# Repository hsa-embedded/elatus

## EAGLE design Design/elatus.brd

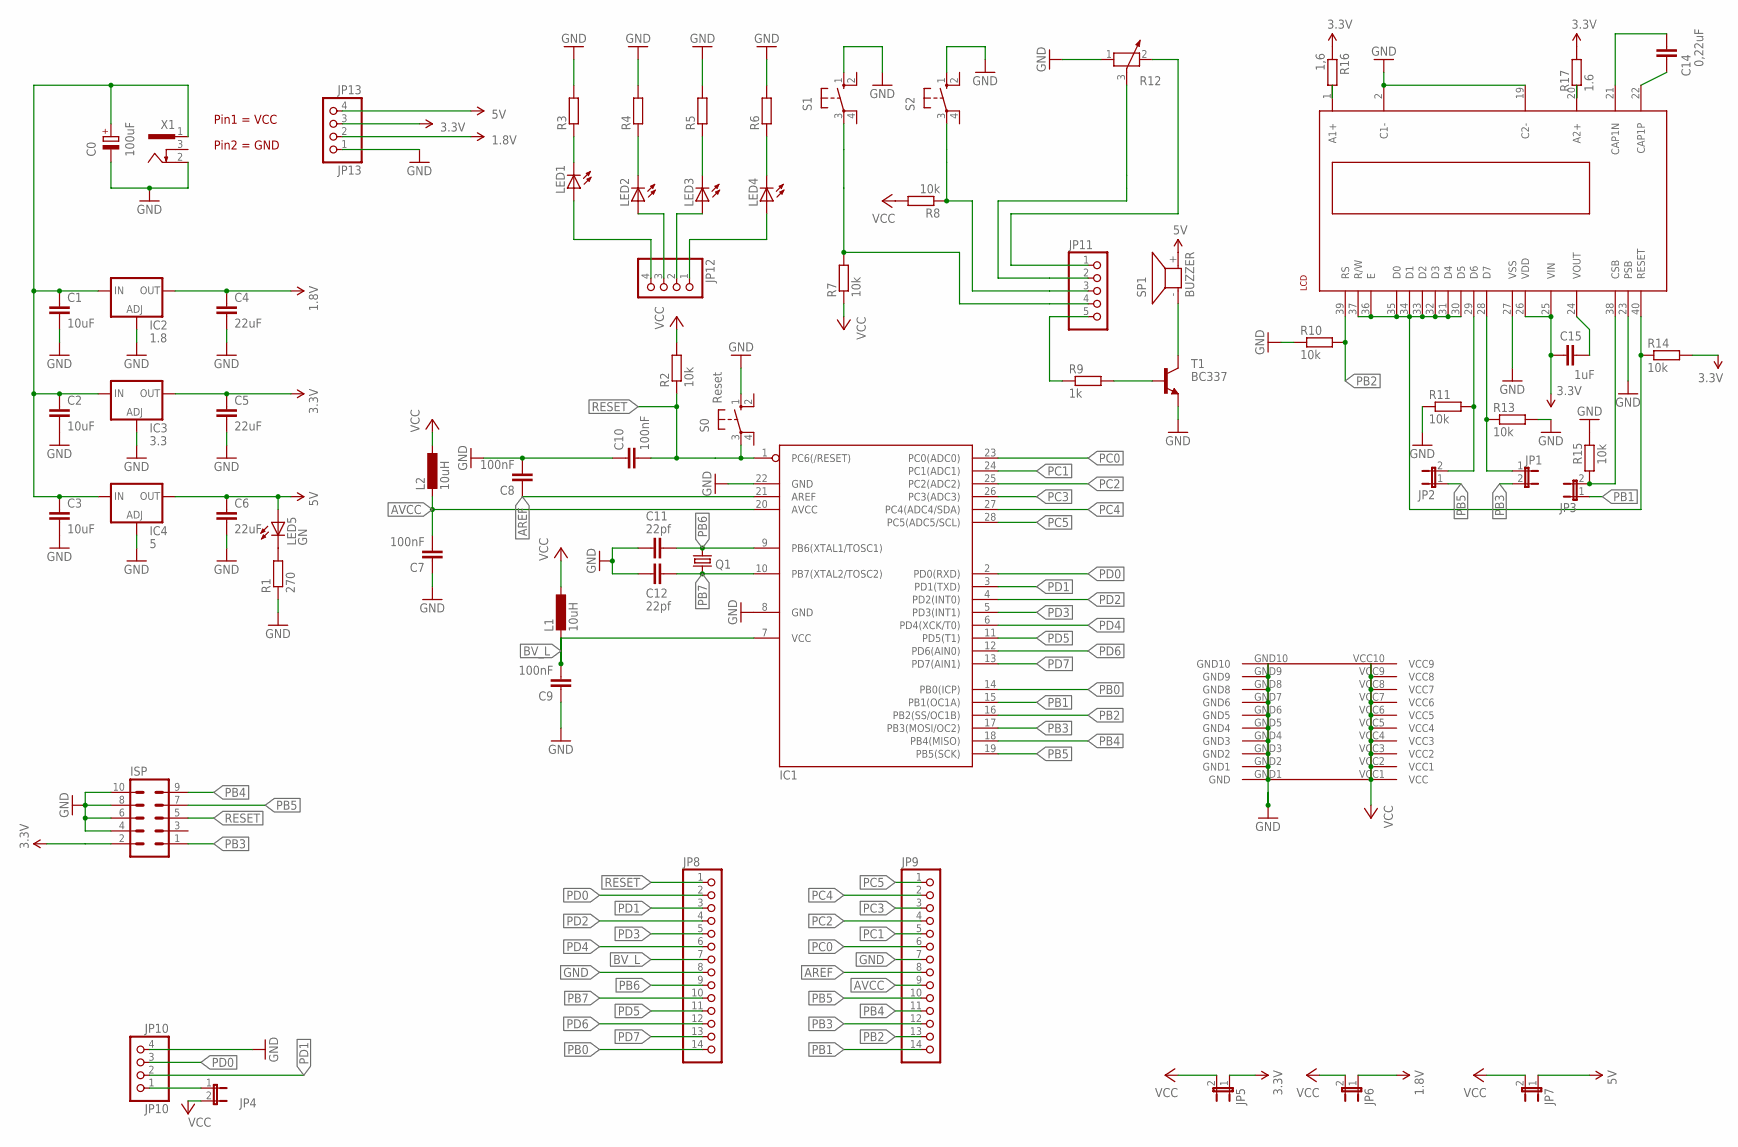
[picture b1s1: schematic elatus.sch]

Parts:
C0: 100uF; RCL_E2,5-7
C1, C2, C3: 10uF; RCL_C025-040X050
C4, C5, C6: 22uF; RCL_C025-040X050
C7, C8, C9, C10: 100nF; RCL_C025-040X050
C11, C12: 22pf; RESISTOR_C050-024X044
C14: 0,22uF; RCL_C025-040X050
C15: 1uF; RCL_C025-040X050
IC1: MEGA8-P; DIL28-3
IC2: 1.8; TO220V
IC3: 3.3; TO220V
IC4: 5; TO220V
ISP: CON-HARTING-ML_ML10
JP1, JP2, JP3, JP4, JP5, JP6, JP7: JP1E; JP1
JP8, JP9: PINHD-1X14; 1X14
JP10: JP10; 1X04
JP11: PINHD-1X5; 1X05
JP12: PINHD-1X4; 1X04
JP13: JP13; 1X04
L1, L2: 10uH; RCL_2200-12.7
LCD: -OPTO_DOGM
LED1, LED2, LED3, LED4: LED_LED3MM
LED5: GN; LED_LED3MM
Q1: CRYSTAL_CRYSTALHC49U70; CRYSTAL_HC49U70
R1: 270; 0207/10
R2, R7, R8, R10, R11, R13, R14, R15: 10k; 0207/10
R3, R4, R5, R6: R-EU_0207/10; 0207/10
R9: 1k; 0207/10
R12: POTENTIOMETER_PT-10; PT-10
R16: 1,6; 0207/10
R17: 1.6; 0207/10
S0: Reset; SWITCH-OMRON_B3F-10XX
S1, S2: SWITCH-OMRON_10-XX; SWITCH-OMRON_B3F-10XX
SP1: BUZZER; BUZZER_F/PMX04A
T1: BC337; TO92
U$3: JP5; RASTER_2_54
X1: CON-CONRAD_733980-62

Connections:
1.8V: C4.1, IC2.2 (OUT), JP6.1, JP13.2
3.3V: C5.1, C15.2, IC3.2 (OUT), ISP.2, JP5.1, JP13.3, LCD.25 (VIN), LCD.26 (VDD), R14.2, R16.1, R17.2
5V: C6.1, IC4.2 (OUT), JP7.1, JP13.4, LED5.A, SP1.+ (2)
AREF: C8.1, IC1.21 (AREF), JP9.8
AVCC: C7.2, IC1.20 (AVCC), JP9.9, L2.2
BV_L: C9.2, IC1.7 (VCC), JP8.7, L1.2
GND: C0.-, C1.2, C2.2, C3.2, C4.2, C5.2, C6.2, C7.1, C8.2, C9.1, C10.1, C11.1, C12.1, IC1.8 (GND), IC1.22 (GND), IC2.1 (ADJ), IC3.1 (ADJ), IC4.1 (ADJ), ISP.4, ISP.6, ISP.8, ISP.10, JP8.8, JP9.7, JP10.4, JP13.1, LCD.2 (C1-), LCD.19 (C2-), LCD.23 (PSB), LCD.27 (VSS), R1.1, R3.2, R4.2, R5.2, R6.2, R10.1, R11.1, R12.1, R13.2, R15.2, S0.1 (S), S1.1 (S), S2.1 (S), T1.1 (E), U$3.GND1 (GND), U$3.GND2 (GND1), U$3.GND3 (GND2), U$3.GND4 (GND3), U$3.GND5 (GND4), U$3.GND6 (GND5), U$3.GND7 (GND6), U$3.GND8, U$3.GND9, U$3.GND10, X1.2
unnamed: LED1.K (C), R3.1
unnamed: LED2.K (C), R4.1
unnamed: JP11.2, R12.3
unnamed: LED3.K (C), R5.1
unnamed: JP11.4, R7.2, S1.3
unnamed: JP12.4, LED1.A
unnamed: JP11.3, R8.1, S2.3
unnamed: LED4.K (C), R6.1
unnamed: JP11.1, R12.2
unnamed: JP12.3, LED2.A
unnamed: JP2.2, LCD.29 (D6), R11.2
unnamed: JP1.1, LCD.28 (D7), R13.1
unnamed: LED5.K (C), R1.2
unnamed: JP4.1, JP10.1
unnamed: JP12.2, LED3.A
unnamed: JP11.5, R9.1
unnamed: JP12.1, LED4.A
unnamed: SP1.- (1), T1.3 (C)
unnamed: LCD.20 (A2+), R17.1
unnamed: C14.2, LCD.21 (CAP1N)
unnamed: C14.1, LCD.22 (CAP1P)
unnamed: C0.+, C1.1, C2.1, C3.1, IC2.3 (IN), IC3.3 (IN), IC4.3 (IN), X1.1
unnamed: LCD.1 (A1+), R16.2
unnamed: LCD.30 (D5), LCD.31 (D4), LCD.32 (D3), LCD.33 (D2), LCD.34 (D1), LCD.35 (D0), LCD.36 (E), LCD.37 (R/W), LCD.40 (RESET), R14.1
unnamed: R9.2, T1.2 (B)
unnamed: C15.1, LCD.24 (VOUT)
unnamed: JP3.2, LCD.38 (CSB), R15.1
PB0: IC1.14 (PB0(ICP)), JP8.14
PB1: IC1.15 (PB1(OC1A)), JP3.1, JP9.14
PB2: IC1.16 (PB2(SS/OC1B)), JP9.13, LCD.39 (RS), R10.2
PB3: IC1.17 (PB3(MOSI/OC2)), ISP.1, JP1.2, JP9.12
PB4: IC1.18 (PB4(MISO)), ISP.9, JP9.11
PB5: IC1.19 (PB5(SCK)), ISP.7, JP2.1, JP9.10
PB6: C11.2, IC1.9 (PB6(XTAL1/TOSC1)), JP8.9, Q1.2
PB7: C12.2, IC1.10 (PB7(XTAL2/TOSC2)), JP8.10, Q1.1
PC0: IC1.23 (PC0(ADC0)), JP9.6
PC1: IC1.24 (PC1(ADC1)), JP9.5
PC2: IC1.25 (PC2(ADC2)), JP9.4
PC3: IC1.26 (PC3(ADC3)), JP9.3
PC4: IC1.27 (PC4(ADC4/SDA)), JP9.2
PC5: IC1.28 (PC5(ADC5/SCL)), JP9.1
PD0: IC1.2 (PD0(RXD)), JP8.2, JP10.3
PD1: IC1.3 (PD1(TXD)), JP8.3, JP10.2
PD2: IC1.4 (PD2(INT0)), JP8.4
PD3: IC1.5 (PD3(INT1)), JP8.5
PD4: IC1.6 (PD4(XCK/T0)), JP8.6
PD5: IC1.11 (PD5(T1)), JP8.11
PD6: IC1.12 (PD6(AIN0)), JP8.12
PD7: IC1.13 (PD7(AIN1)), JP8.13
RESET: C10.2, IC1.1 (PC6(/RESET)), ISP.5, JP8.1, R2.1, S0.3
VCC: JP4.2, JP5.2, JP6.2, JP7.2, L1.1, L2.1, R2.2, R7.1, R8.2, U$3.VCC1 (VCC), U$3.VCC2 (VCC1), U$3.VCC3 (VCC2), U$3.VCC4 (VCC3), U$3.VCC5 (VCC4), U$3.VCC6 (VCC5), U$3.VCC7 (VCC6), U$3.VCC8 (VCC7), U$3.VCC9 (VCC8), U$3.VCC10 (VCC9)

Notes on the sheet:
Pin1 = VCC
Pin2 = GND

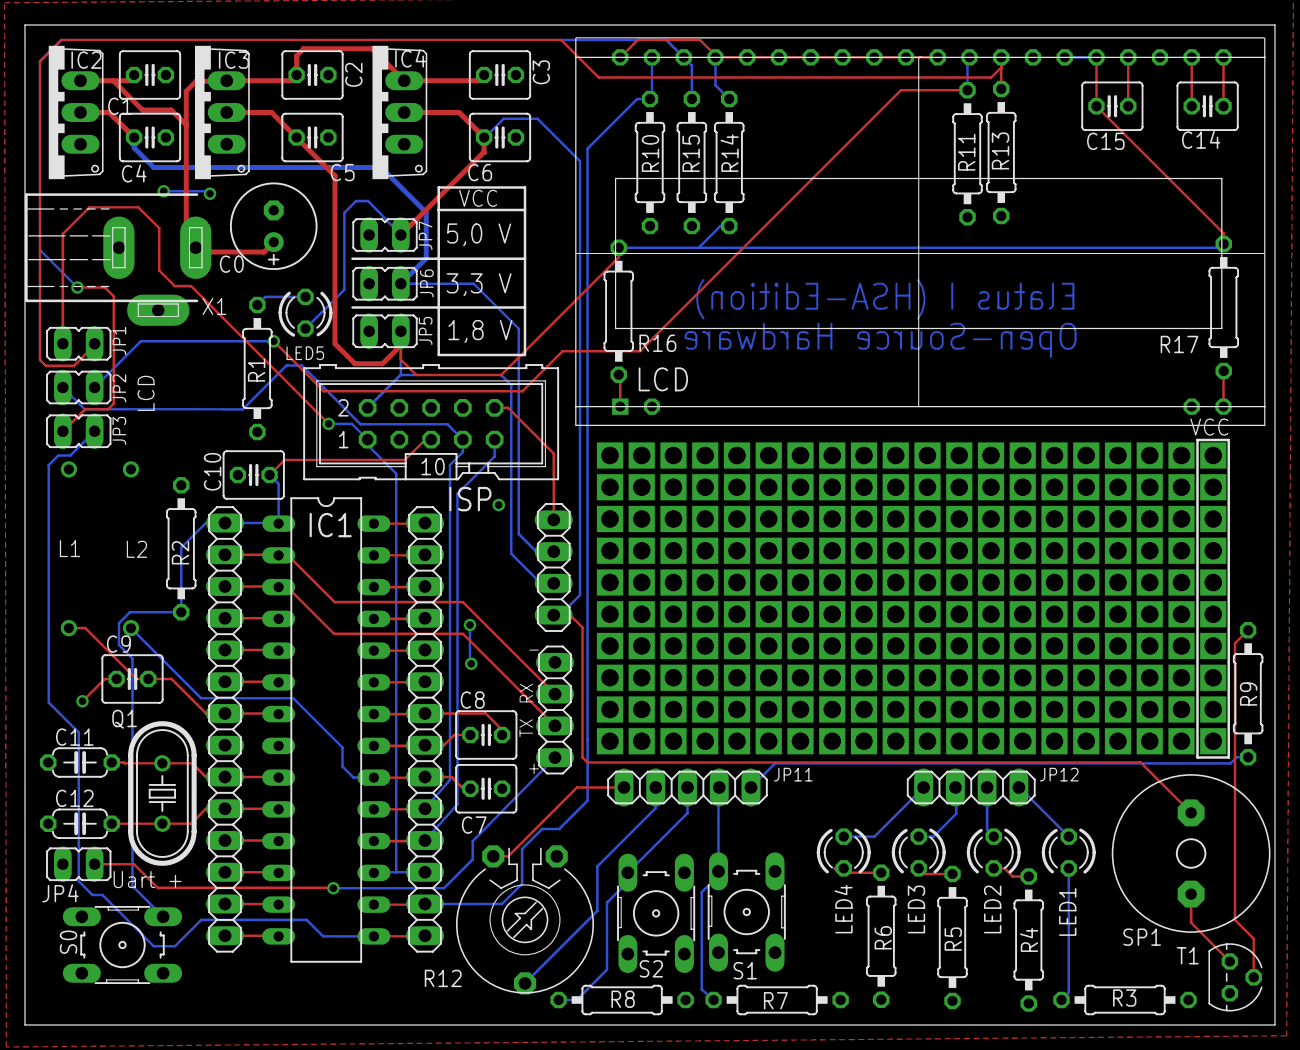
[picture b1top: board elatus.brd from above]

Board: 2 copper layers, 100.0 x 80.0 mm, 66 parts (0 on the bottom side), 58 nets.

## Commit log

2015-01-07 new file: Design/Doc/Bauteile_Farnell.ods new file: Design/Doc/Bauteile_RS-Componets.ods new file: Design/Doc/Bauteile_Reichelt.ods new file: Design/Doc/Status_elatus_boards.ods new file: Design/Doc/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
